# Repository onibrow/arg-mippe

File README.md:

# Modular Integration Platform for Printed Electronics

##  Burn  In

Functional with indicator LEDs to burn in Arduino bootloader to any ISP contact pad enabled microcontroller board.

## MIPPE Base

Two Versions: ATMega328 \& ATMega32U4. The 328 does not have a built in USB interface and has a larger footprint size at a 32 pin QFP. The 32u4 does support native USB with a higher price tag and smaller footprint 44 pin QFN.

To flash, plug in the Burn In tool and run `bootloader.sh` script. Tap on a fully populated microcontrller enabled board using ISP contact pads and pogo pins. Select the appropriate microcontroller to start flashing. The 328 will only take about 15 seconds, while the 32u4 takes an upwards of 2 minutes

## OLED PMIC

An OLED driver that can do current control and limiting.

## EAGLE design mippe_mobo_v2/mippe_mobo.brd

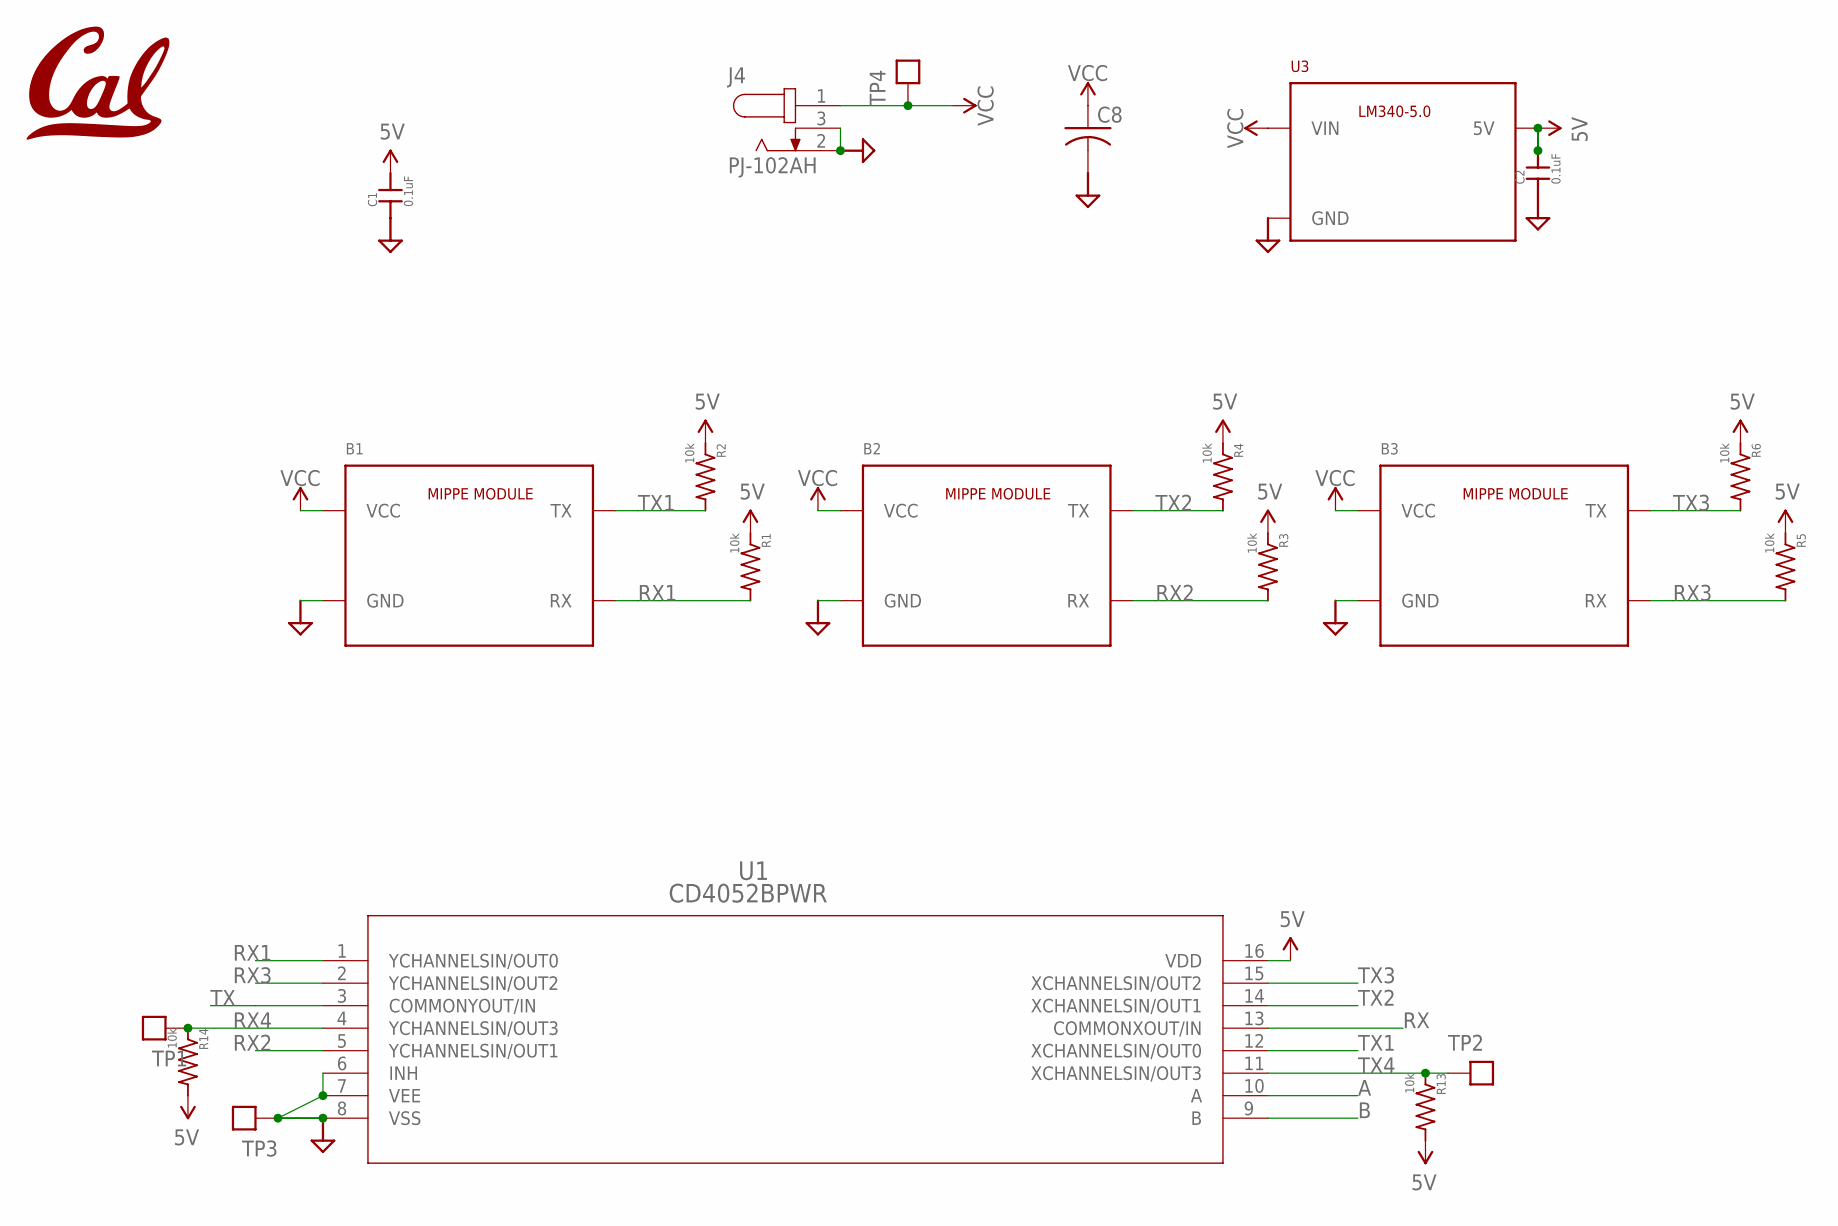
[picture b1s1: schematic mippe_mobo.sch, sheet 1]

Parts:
B1, B2, B3: MIPPE_MOD
C1: 0.1uF; 0402-CAP
C2: 0.1uF; 0603-CAP
C8: CAP_ELEC_3MM_SMD; CAP_3MM
J4: PJ-102AH; CUI_PJ-102AH
L1: UCB_CAL500MIL; UCB_CAL_500MIL
R1, R2, R3, R4, R5, R6, R13, R14: 10k; R0402
TP1, TP2, TP3, TP4: TEST_POINTTHRU; TEST_POINT
U1: CD4052BPWR; PW16
U3: LM340MPX-5.0230; SOT230P700X180-4N

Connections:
5V: C1.2, C2.2, R1.1, R2.1, R3.1, R4.1, R5.1, R6.1, R13.2, R14.2, U1.16 (VDD), U3.3 (5V)
A: U1.10 (A); also elsewhere on the board
B: U1.9 (B); also elsewhere on the board
GND: B1.GND@0 (GND), B1.GND@1 (GND), B1.GND@2 (GND), B1.GND@3 (GND), B2.GND@0 (GND), B2.GND@1 (GND), B2.GND@2 (GND), B2.GND@3 (GND), B3.GND@0 (GND), B3.GND@1 (GND), B3.GND@2 (GND), B3.GND@3 (GND), C1.1, C2.1, C8.NEG, J4.2, J4.3, TP3.1, U1.6 (INH), U1.7 (VEE), U1.8 (VSS), U3.2 (GND), U3.4 (GND); also elsewhere on the board
RX: U1.13 (COMMONXOUT/IN); also elsewhere on the board
RX1: B1.RX, R1.2, U1.1 (YCHANNELSIN/OUT0)
RX2: B2.RX, R3.2, U1.5 (YCHANNELSIN/OUT1)
RX3: B3.RX, R5.2, U1.2 (YCHANNELSIN/OUT2)
RX4: R14.1, TP1.1, U1.4 (YCHANNELSIN/OUT3)
TX: U1.3 (COMMONYOUT/IN); also elsewhere on the board
TX1: B1.TX, R2.2, U1.12 (XCHANNELSIN/OUT0)
TX2: B2.TX, R4.2, U1.14 (XCHANNELSIN/OUT1)
TX3: B3.TX, R6.2, U1.15 (XCHANNELSIN/OUT2)
TX4: R13.1, TP2.1, U1.11 (XCHANNELSIN/OUT3)
VCC: B1.VCC@0 (VCC), B1.VCC@1 (VCC), B1.VCC@2 (VCC), B1.VCC@3 (VCC), B2.VCC@0 (VCC), B2.VCC@1 (VCC), B2.VCC@2 (VCC), B2.VCC@3 (VCC), B3.VCC@0 (VCC), B3.VCC@1 (VCC), B3.VCC@2 (VCC), B3.VCC@3 (VCC), C8.POS, J4.1, TP4.1, U3.1 (VIN)

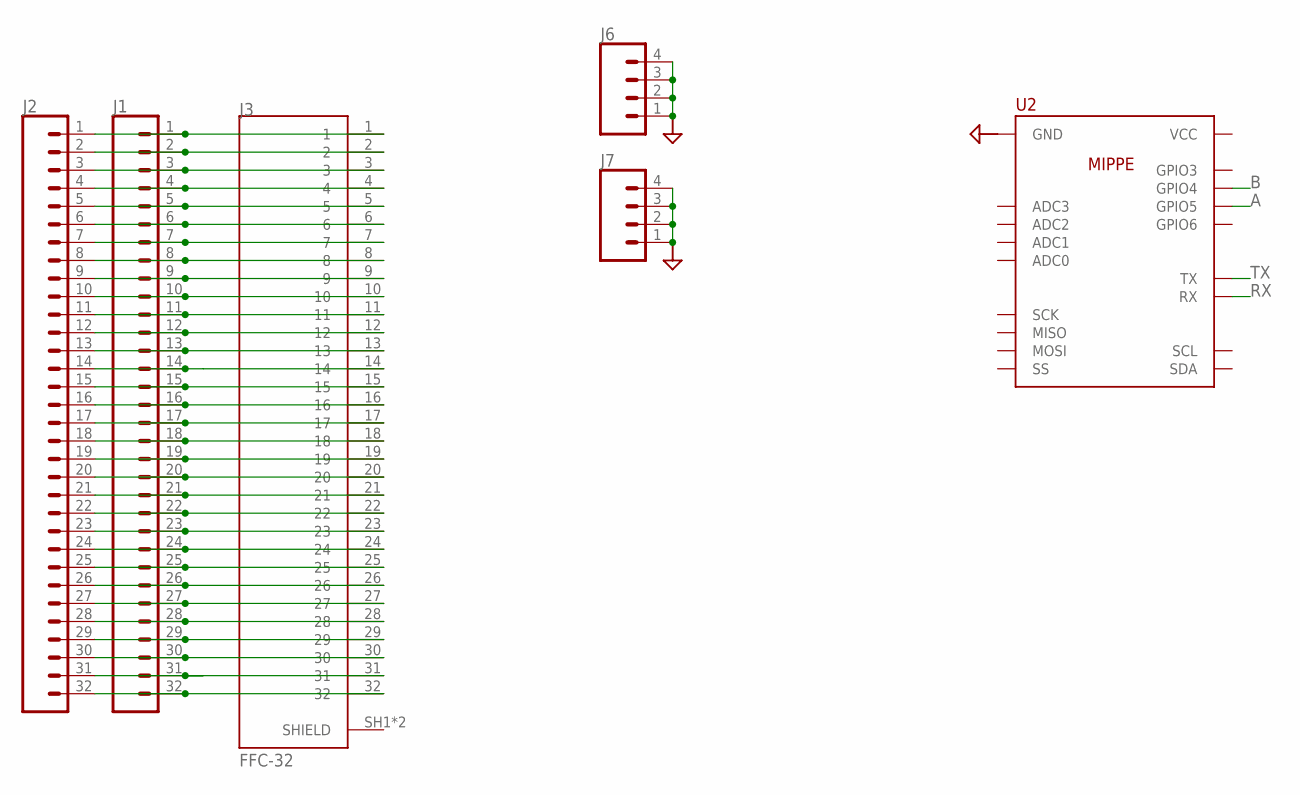
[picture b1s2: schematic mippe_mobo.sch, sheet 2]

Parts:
J1, J2: CONN_32; 1X32
J3: FFC-32; MOLEX_503480-3200
J6, J7: CONN_04; 1X04
U2: MIPPE

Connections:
A: U2.GPIO5; also elsewhere on the board
B: U2.GPIO4; also elsewhere on the board
GND: J6.1, J6.2, J6.3, J6.4, J7.1, J7.2, J7.3, J7.4, U2.GND@0 (GND), U2.GND@1 (GND); also elsewhere on the board
unnamed: J1.1, J2.1, J3.1
unnamed: J1.2, J2.2, J3.2
unnamed: J1.3, J2.3, J3.3
unnamed: J1.4, J2.4, J3.4
unnamed: J1.5, J2.5, J3.5
unnamed: J1.6, J2.6, J3.6
unnamed: J1.7, J2.7, J3.7
unnamed: J1.8, J2.8, J3.8
unnamed: J1.9, J2.9, J3.9
unnamed: J1.10, J2.10, J3.10
unnamed: J1.11, J2.11, J3.11
unnamed: J1.12, J2.12, J3.12
unnamed: J1.13, J2.13, J3.13
unnamed: J1.14, J2.14, J3.14
unnamed: J1.15, J2.15, J3.15
unnamed: J1.16, J2.16, J3.16
unnamed: J1.17, J2.17, J3.17
unnamed: J1.18, J2.18, J3.18
unnamed: J1.19, J2.19, J3.19
unnamed: J1.20, J2.20, J3.20
unnamed: J1.21, J2.21, J3.21
unnamed: J1.22, J2.22, J3.22
unnamed: J1.23, J2.23, J3.23
unnamed: J1.24, J2.24, J3.24
unnamed: J1.25, J2.25, J3.25
unnamed: J1.26, J2.26, J3.26
unnamed: J1.27, J2.27, J3.27
unnamed: J1.28, J2.28, J3.28
unnamed: J1.29, J2.29, J3.29
unnamed: J1.30, J2.30, J3.30
unnamed: J1.31, J2.31, J3.31
unnamed: J1.32, J2.32, J3.32
RX: U2.RX; also elsewhere on the board
TX: U2.TX; also elsewhere on the board

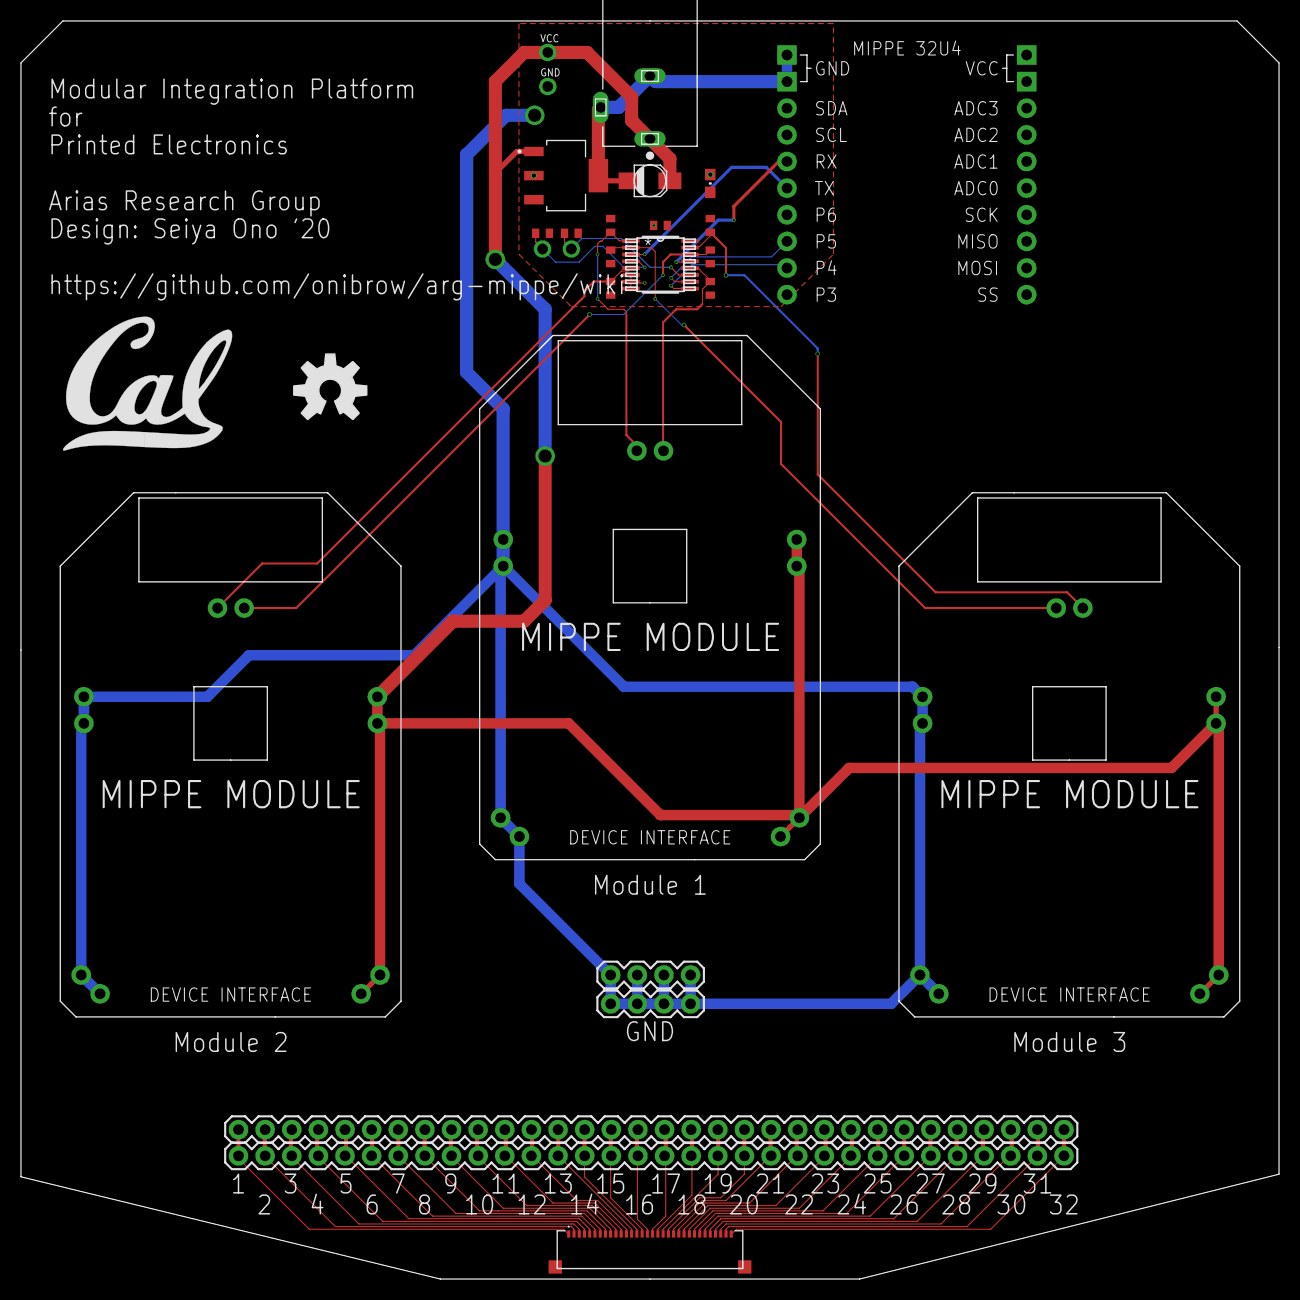
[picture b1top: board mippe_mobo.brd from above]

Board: 2 copper layers, 120.0 x 120.0 mm, 29 parts (0 on the bottom side), 47 nets.

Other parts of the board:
U$17: OSHW-LOGO-L

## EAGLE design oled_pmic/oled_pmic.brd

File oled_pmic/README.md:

# OLED PMIC

Power Management IC OLED Driver Board

Using the [AL5801](https://www.digikey.com/product-detail/en/diodes-incorporated/AL5801W6-7/AL5801W6-7DICT-ND/3481118), we can supply a high voltage (9V) to the OLEDs while controlling the current through it, up to 350mA. To limit the current through Q2 (see figure below) R\_bias must be set to 52.5k when running Vcc = 9V. The sense resistor R\_ext will be set to a minimum of 1.6 Ohms for full 350mA operation.

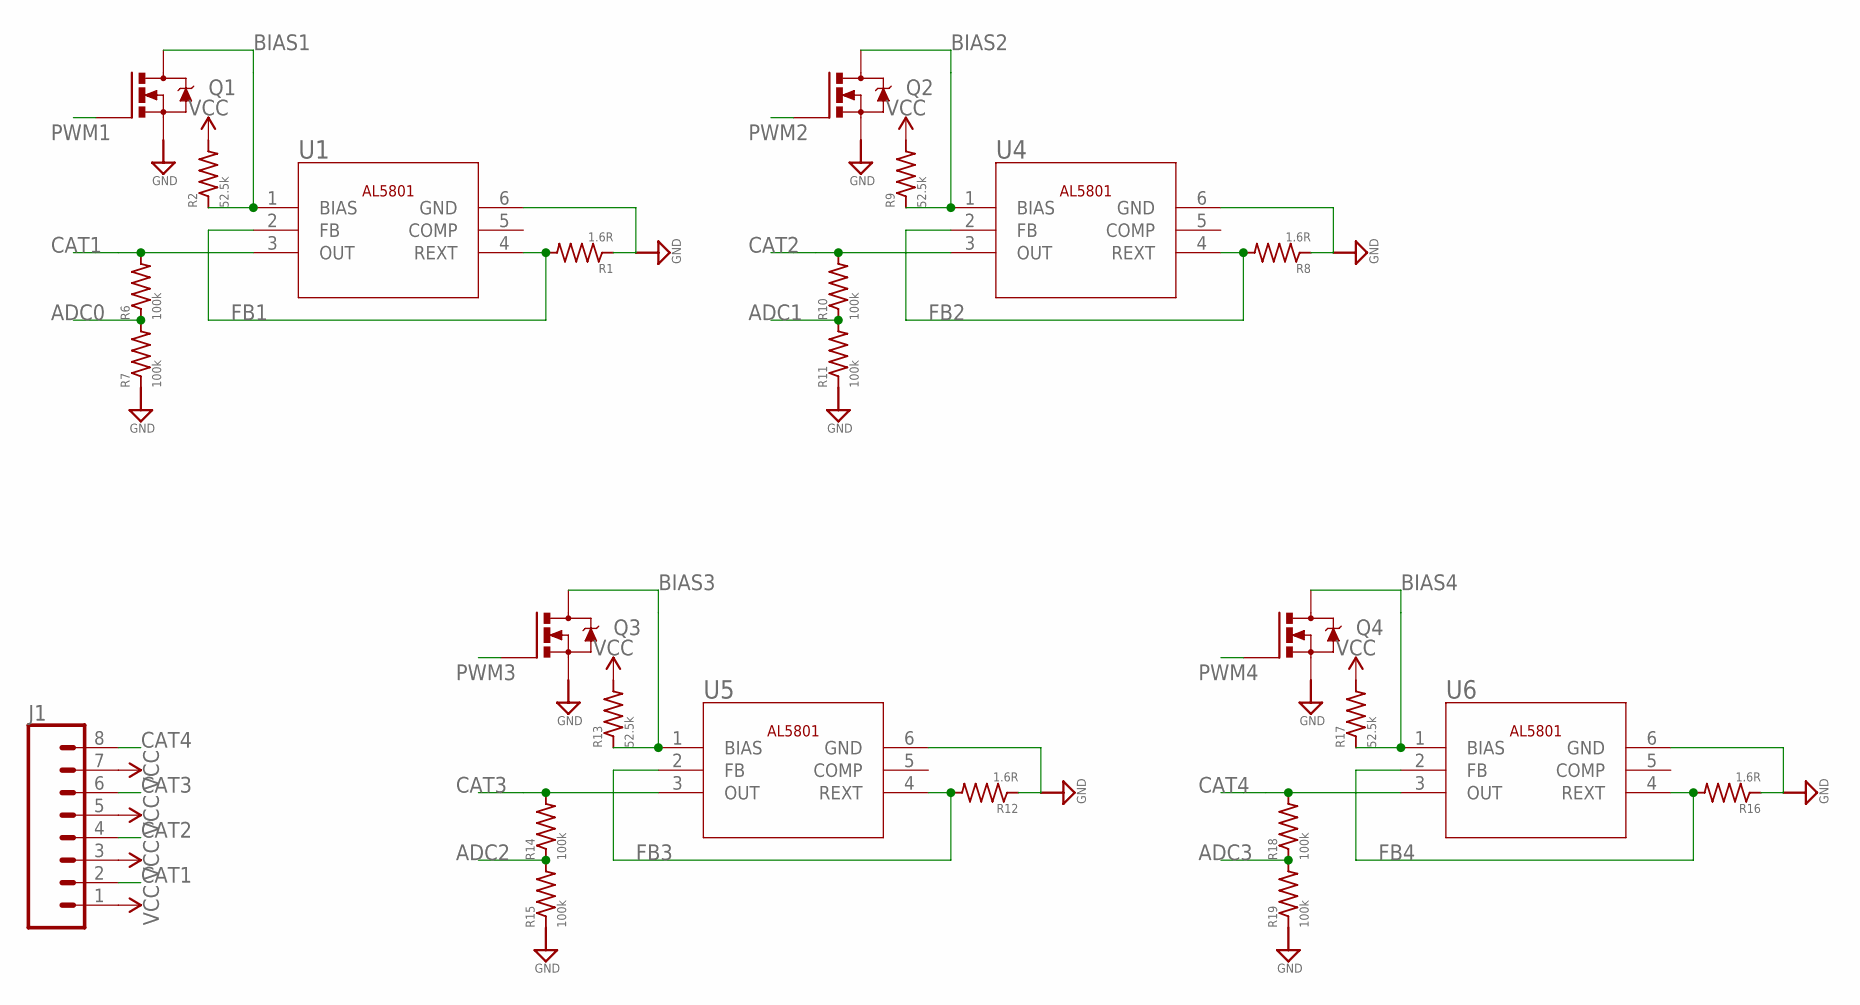
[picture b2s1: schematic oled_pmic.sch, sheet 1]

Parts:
J1: CONN_08"; 1X08
Q1, Q2, Q3, Q4: N-CHANNEL-MOSFETSOT23-3; SOT23-3
R1, R8, R12, R16: 1.6R; 0603-RES
R2, R9, R13, R17: 52.5k; 0603-RES
R6, R7, R10, R11, R14, R15, R18, R19: 100k; R0402
U1, U4, U5, U6: AL5801W6-7; SOT26

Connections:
ADC0: R6.1, R7.2; also elsewhere on the board
ADC1: R10.1, R11.2; also elsewhere on the board
ADC2: R14.1, R15.2; also elsewhere on the board
ADC3: R18.1, R19.2; also elsewhere on the board
BIAS1: Q1.3 (D), R2.1, U1.1 (BIAS)
BIAS2: Q2.3 (D), R9.1, U4.1 (BIAS)
BIAS3: Q3.3 (D), R13.1, U5.1 (BIAS)
BIAS4: Q4.3 (D), R17.1, U6.1 (BIAS)
CAT1: J1.2, R6.2, U1.3 (OUT)
CAT2: J1.4, R10.2, U4.3 (OUT)
CAT3: J1.6, R14.2, U5.3 (OUT)
CAT4: J1.8, R18.2, U6.3 (OUT)
FB1: R1.2, U1.2 (FB), U1.4 (REXT)
FB2: R8.2, U4.2 (FB), U4.4 (REXT)
FB3: R12.2, U5.2 (FB), U5.4 (REXT)
FB4: R16.2, U6.2 (FB), U6.4 (REXT)
GND: Q1.2 (S), Q2.2 (S), Q3.2 (S), Q4.2 (S), R1.1, R7.1, R8.1, R11.1, R12.1, R15.1, R16.1, R19.1, U1.6 (GND), U4.6 (GND), U5.6 (GND), U6.6 (GND); also elsewhere on the board
PWM1: Q1.1 (G); also elsewhere on the board
PWM2: Q2.1 (G); also elsewhere on the board
PWM3: Q3.1 (G); also elsewhere on the board
PWM4: Q4.1 (G); also elsewhere on the board
VCC: J1.1, J1.3, J1.5, J1.7, R2.2, R9.2, R13.2, R17.2; also elsewhere on the board

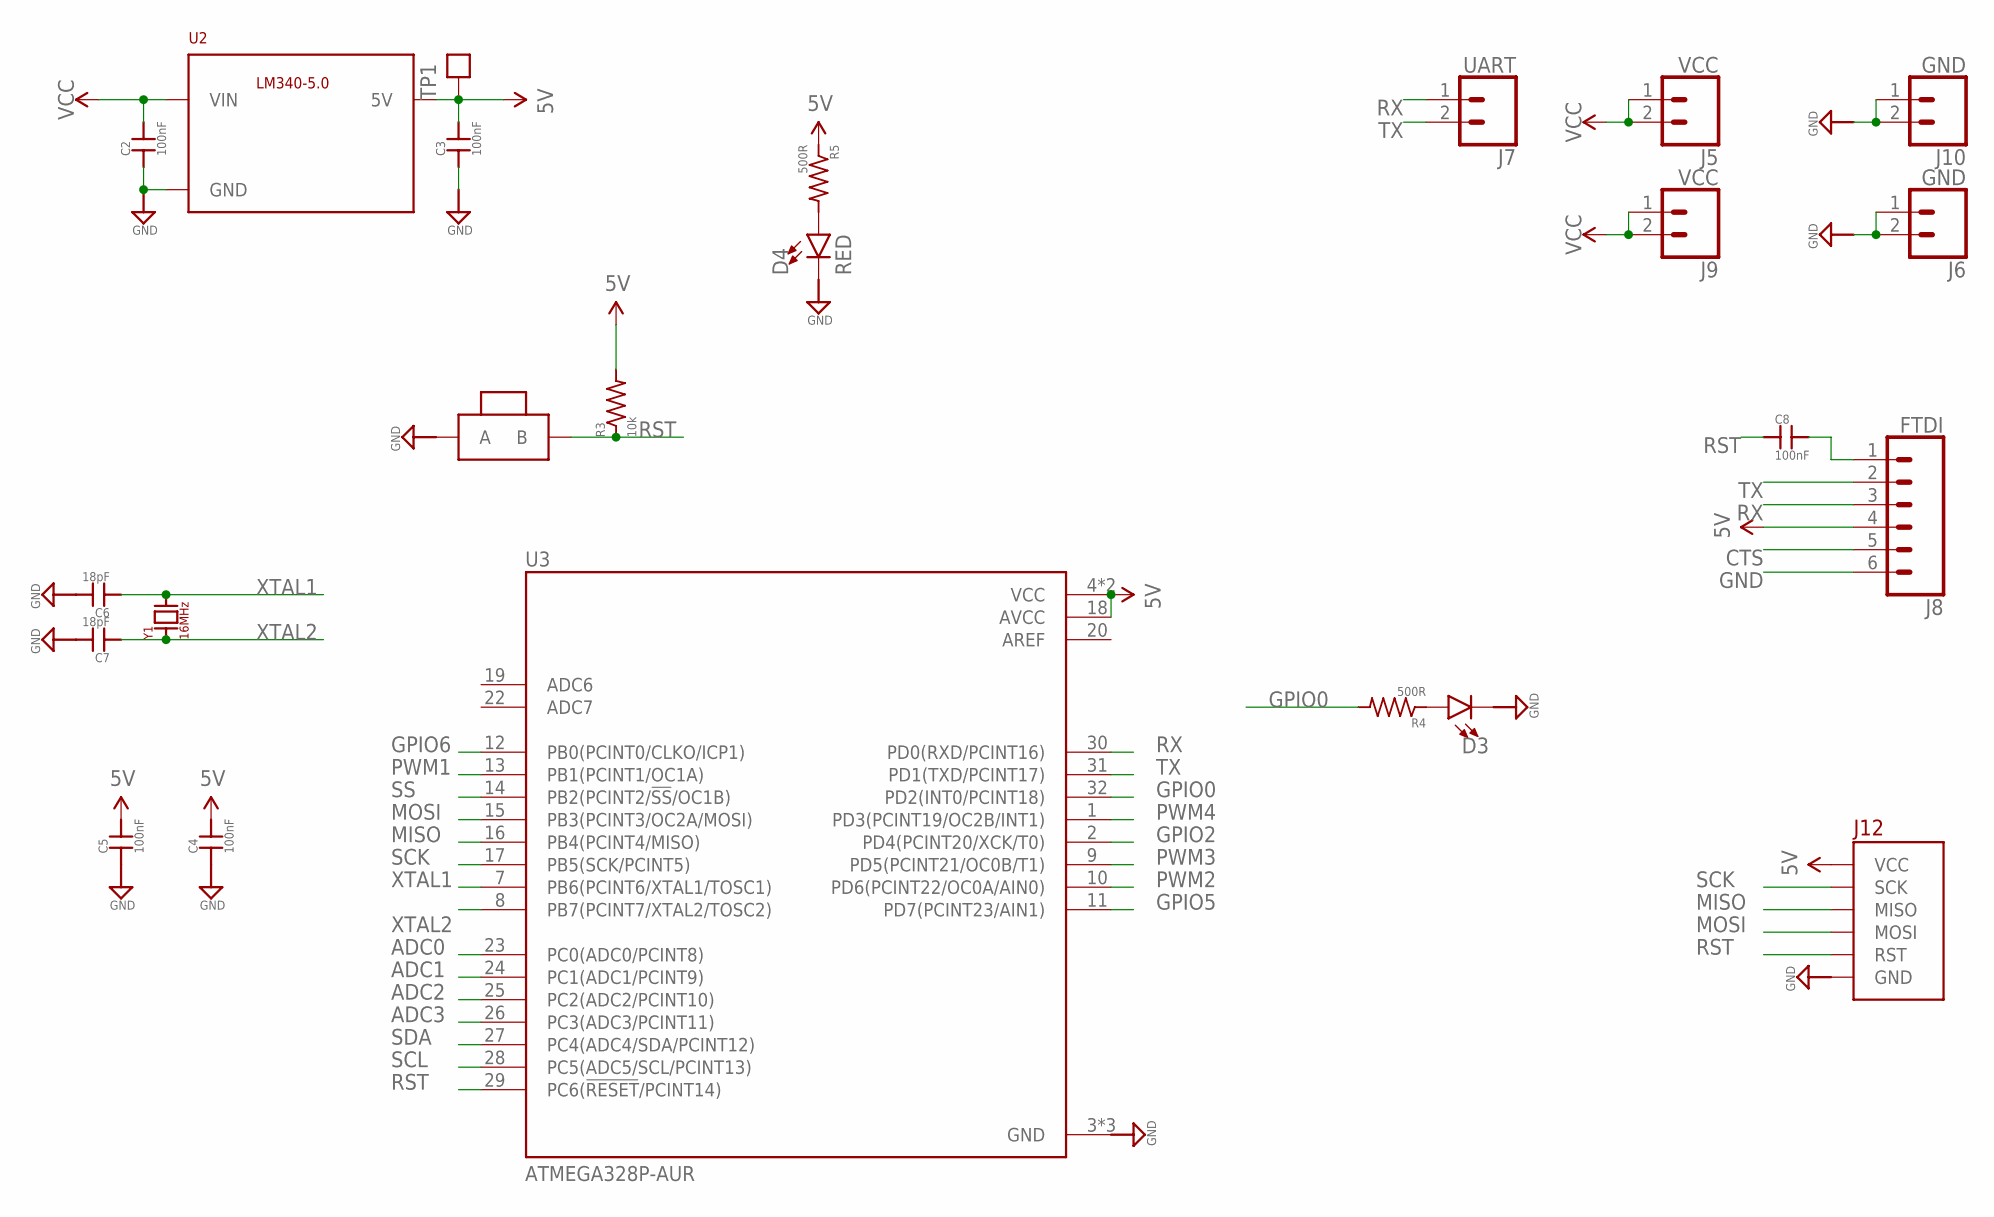
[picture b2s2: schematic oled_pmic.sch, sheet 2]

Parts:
C2, C3, C4, C5, C8: 100nF; 0402-CAP
C6, C7: 18pF; 0402-CAP
D3: LED0603; LED-0603
D4: RED; LED-0603
J5, J9: VCC; 1X02
J6, J10: GND; 1X02
J7: UART; 1X02
J8: FTDI; 1X06_NO_SILK
J12: BURNIN
R3: 10k; R0402
R4, R5: 500R; R0402
SW1: BTN-PTS810; BTN_PTS810
TP1: TEST_POINTTHRU; TEST_POINT
U2: LM340MPX-5.0230; SOT230P700X180-4N
U3: ATMEGA328P-AUR; QFP80P900X900X120-32N
Y1: 16MHz; XTAL500X320X130N

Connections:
5V: C3.2, C4.2, C5.2, J8.4, J12.3.3V (VCC), R3.2, R5.1, TP1.1, U2.3 (5V), U3.4 (VCC), U3.6 (VCC), U3.18 (AVCC)
ADC0: U3.23 (PC0(ADC0/PCINT8)); also elsewhere on the board
ADC1: U3.24 (PC1(ADC1/PCINT9)); also elsewhere on the board
ADC2: U3.25 (PC2(ADC2/PCINT10)); also elsewhere on the board
ADC3: U3.26 (PC3(ADC3/PCINT11)); also elsewhere on the board
AREF: U3.20 (AREF)
CTS: J8.5
GND: C2.1, C3.1, C4.1, C5.1, C6.2, C7.2, D3.C, D4.C, J6.1, J6.2, J8.6, J10.1, J10.2, J12.GND, SW1.1 (A), SW1.2 (A), U2.2 (GND), U2.4 (GND), U3.3 (GND), U3.5 (GND), U3.21 (GND); also elsewhere on the board
GPIO0: R4.2, U3.32 (PD2(INT0/PCINT18))
GPIO2: U3.2 (PD4(PCINT20/XCK/T0))
GPIO5: U3.11 (PD7(PCINT23/AIN1))
GPIO6: U3.12 (PB0(PCINT0/CLKO/ICP1))
MISO: J12.MISO, U3.16 (PB4(PCINT4/MISO))
MOSI: J12.MOSI, U3.15 (PB3(PCINT3/OC2A/MOSI))
unnamed: D3.A, R4.1
unnamed: D4.A, R5.2
unnamed: C8.2, J8.1
PWM1: U3.13 (PB1(PCINT1/OC1A)); also elsewhere on the board
PWM2: U3.10 (PD6(PCINT22/OC0A/AIN0)); also elsewhere on the board
PWM3: U3.9 (PD5(PCINT21/OC0B/T1)); also elsewhere on the board
PWM4: U3.1 (PD3(PCINT19/OC2B/INT1)); also elsewhere on the board
RST: C8.1, J12.RST, R3.1, SW1.3 (B), SW1.4 (B), U3.29 (PC6(!RESET!/PCINT14))
RX: J7.1, J8.3, U3.30 (PD0(RXD/PCINT16))
SCK: J12.SCK, U3.17 (PB5(SCK/PCINT5))
SCL: U3.28 (PC5(ADC5/SCL/PCINT13))
SDA: U3.27 (PC4(ADC4/SDA/PCINT12))
SS: U3.14 (PB2(PCINT2/!SS!/OC1B))
TX: J7.2, J8.2, U3.31 (PD1(TXD/PCINT17))
VCC: C2.2, J5.1, J5.2, J9.1, J9.2, U2.1 (VIN); also elsewhere on the board
XTAL1: C6.1, U3.7 (PB6(PCINT6/XTAL1/TOSC1)), Y1.2 (B)
XTAL2: C7.1, U3.8 (PB7(PCINT7/XTAL2/TOSC2)), Y1.1 (A)

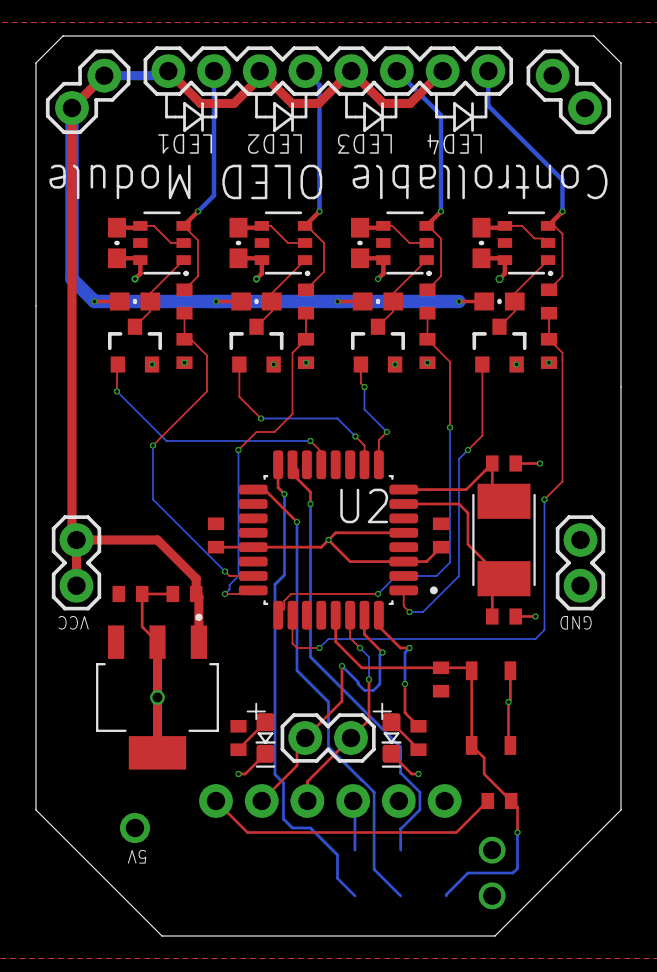
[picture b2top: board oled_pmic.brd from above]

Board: 2 copper layers, 32.5 x 50.0 mm, 49 parts (0 on the bottom side), 35 nets.

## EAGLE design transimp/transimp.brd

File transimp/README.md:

# Transimpedance Amplifier

One of the key applications for a transimpedance amplifier is the readout of a photodiode. The group has looked into using our printed photodiodes in a pulse oximetry setup - meaningful data can only be drawn from [PPG measurements exceeding 60Hz ](https://ieeexplore.ieee.org/stamp/stamp.jsp?arnumber=8704947).

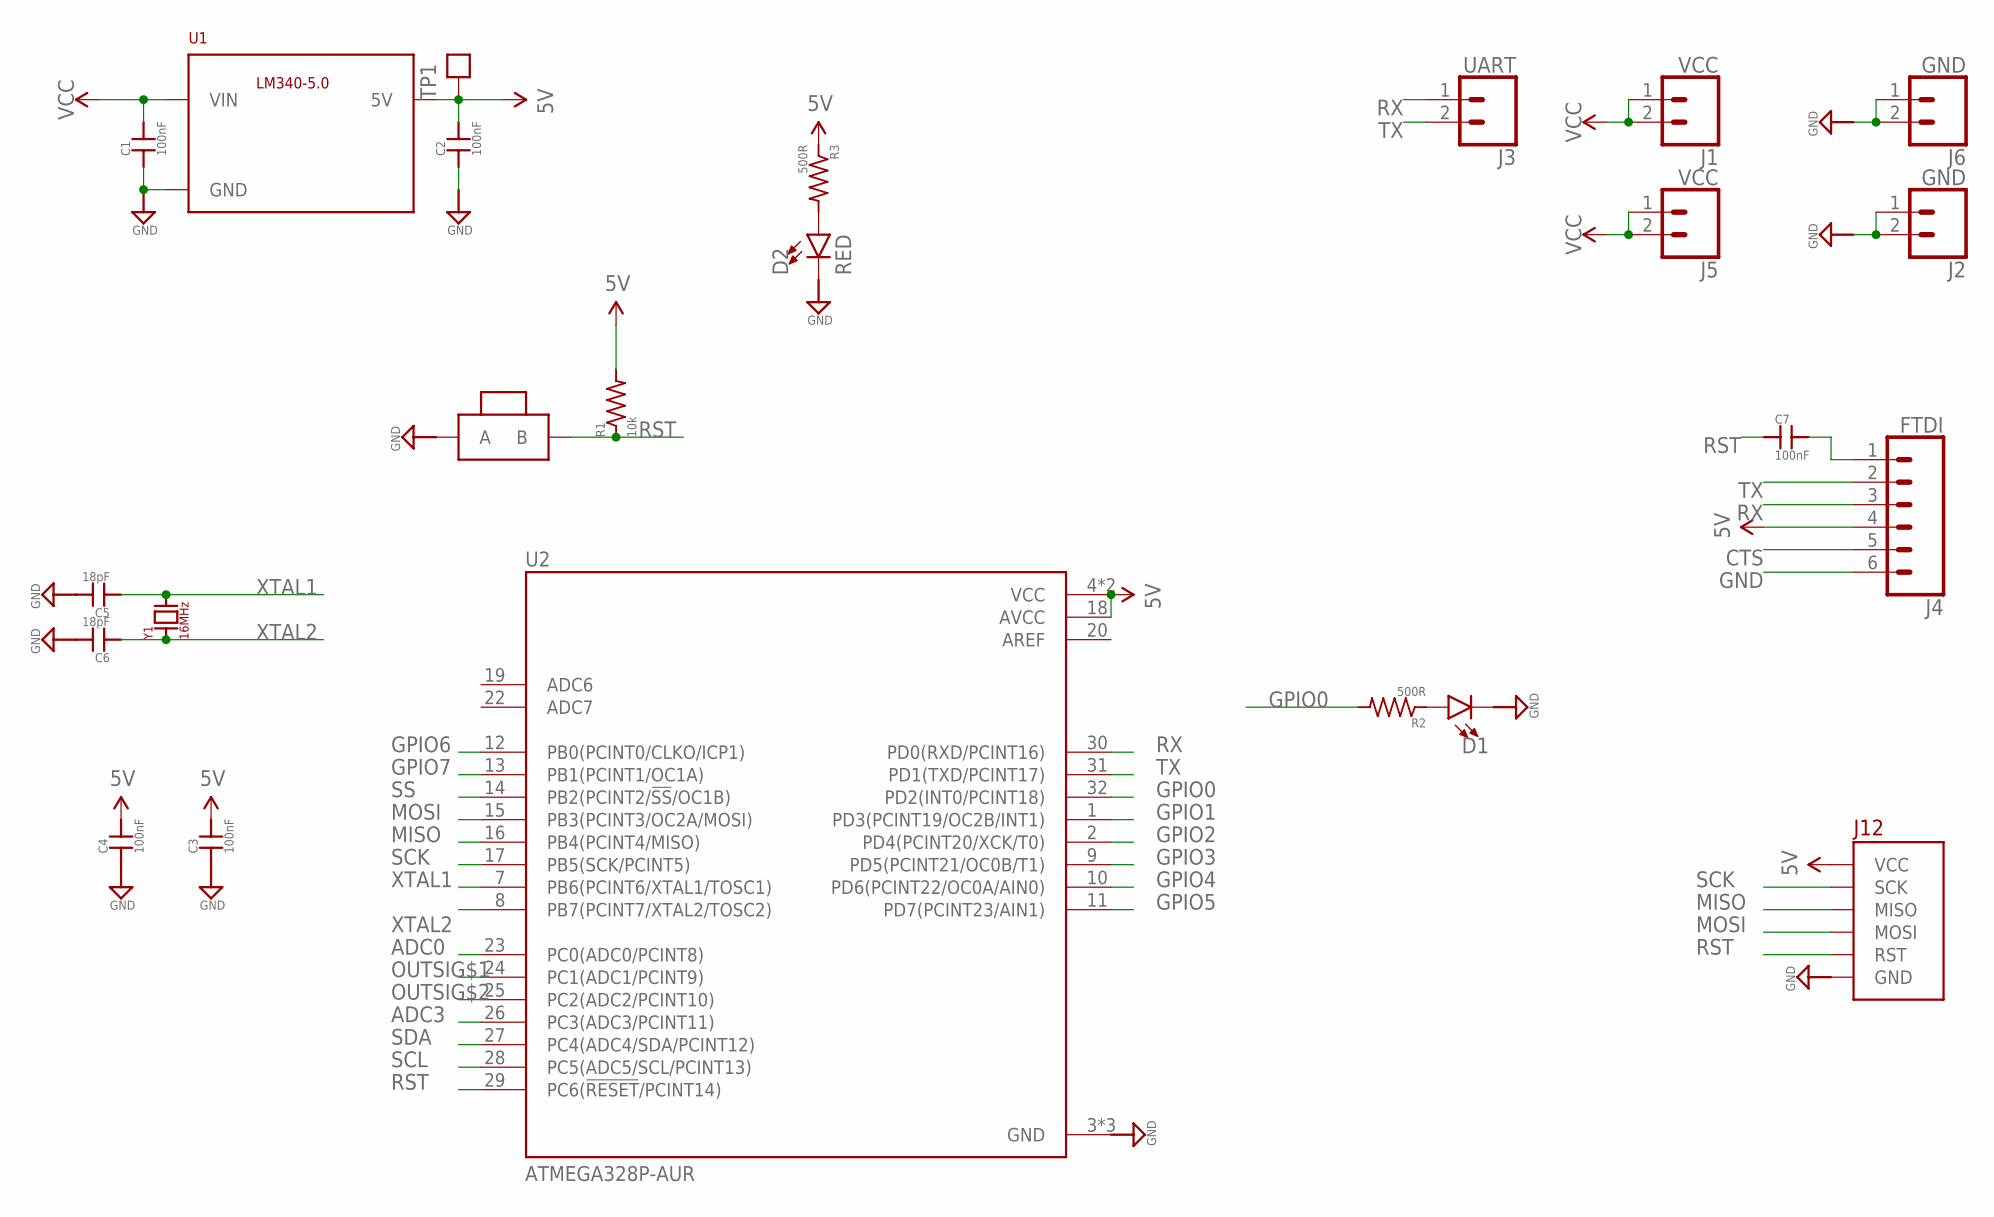
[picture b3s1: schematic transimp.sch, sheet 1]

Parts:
C1, C2, C3, C4, C7: 100nF; 0402-CAP
C5, C6: 18pF; 0402-CAP
D1: LED0603; LED-0603
D2: RED; LED-0603
J1, J5: VCC; 1X02
J2, J6: GND; 1X02
J3: UART; 1X02
J4: FTDI; 1X06_NO_SILK
J12: BURNIN
R1: 10k; R0402
R2, R3: 500R; R0402
SW1: BTN-PTS810; BTN_PTS810
TP1: TEST_POINTTHRU; TEST_POINT
U1: LM340MPX-5.0230; SOT230P700X180-4N
U2: ATMEGA328P-AUR; QFP80P900X900X120-32N
Y1: 16MHz; XTAL500X320X130N

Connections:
5V: C2.2, C3.2, C4.2, J4.4, J12.3.3V (VCC), R1.2, R3.1, TP1.1, U1.3 (5V), U2.4 (VCC), U2.6 (VCC), U2.18 (AVCC); also elsewhere on the board
ADC0: U2.23 (PC0(ADC0/PCINT8))
ADC3: U2.26 (PC3(ADC3/PCINT11))
AREF: U2.20 (AREF)
CTS: J4.5
GND: C1.1, C2.1, C3.1, C4.1, C5.2, C6.2, D1.C, D2.C, J2.1, J2.2, J4.6, J6.1, J6.2, J12.GND, SW1.1 (A), SW1.2 (A), U1.2 (GND), U1.4 (GND), U2.3 (GND), U2.5 (GND), U2.21 (GND); also elsewhere on the board
GPIO0: R2.2, U2.32 (PD2(INT0/PCINT18))
GPIO1: U2.1 (PD3(PCINT19/OC2B/INT1))
GPIO2: U2.2 (PD4(PCINT20/XCK/T0))
GPIO3: U2.9 (PD5(PCINT21/OC0B/T1))
GPIO4: U2.10 (PD6(PCINT22/OC0A/AIN0))
GPIO5: U2.11 (PD7(PCINT23/AIN1))
GPIO6: U2.12 (PB0(PCINT0/CLKO/ICP1))
GPIO7: U2.13 (PB1(PCINT1/OC1A))
MISO: J12.MISO, U2.16 (PB4(PCINT4/MISO))
MOSI: J12.MOSI, U2.15 (PB3(PCINT3/OC2A/MOSI))
unnamed: D1.A, R2.1
unnamed: D2.A, R3.2
unnamed: C7.2, J4.1
OUTSIG$1: U2.24 (PC1(ADC1/PCINT9)); also elsewhere on the board
OUTSIG$2: U2.25 (PC2(ADC2/PCINT10)); also elsewhere on the board
RST: C7.1, J12.RST, R1.1, SW1.3 (B), SW1.4 (B), U2.29 (PC6(!RESET!/PCINT14))
RX: J3.1, J4.3, U2.30 (PD0(RXD/PCINT16))
SCK: J12.SCK, U2.17 (PB5(SCK/PCINT5))
SCL: U2.28 (PC5(ADC5/SCL/PCINT13)); also elsewhere on the board
SDA: U2.27 (PC4(ADC4/SDA/PCINT12)); also elsewhere on the board
SS: U2.14 (PB2(PCINT2/!SS!/OC1B))
TX: J3.2, J4.2, U2.31 (PD1(TXD/PCINT17))
VCC: C1.2, J1.1, J1.2, J5.1, J5.2, U1.1 (VIN)
XTAL1: C5.1, U2.7 (PB6(PCINT6/XTAL1/TOSC1)), Y1.2 (B)
XTAL2: C6.1, U2.8 (PB7(PCINT7/XTAL2/TOSC2)), Y1.1 (A)

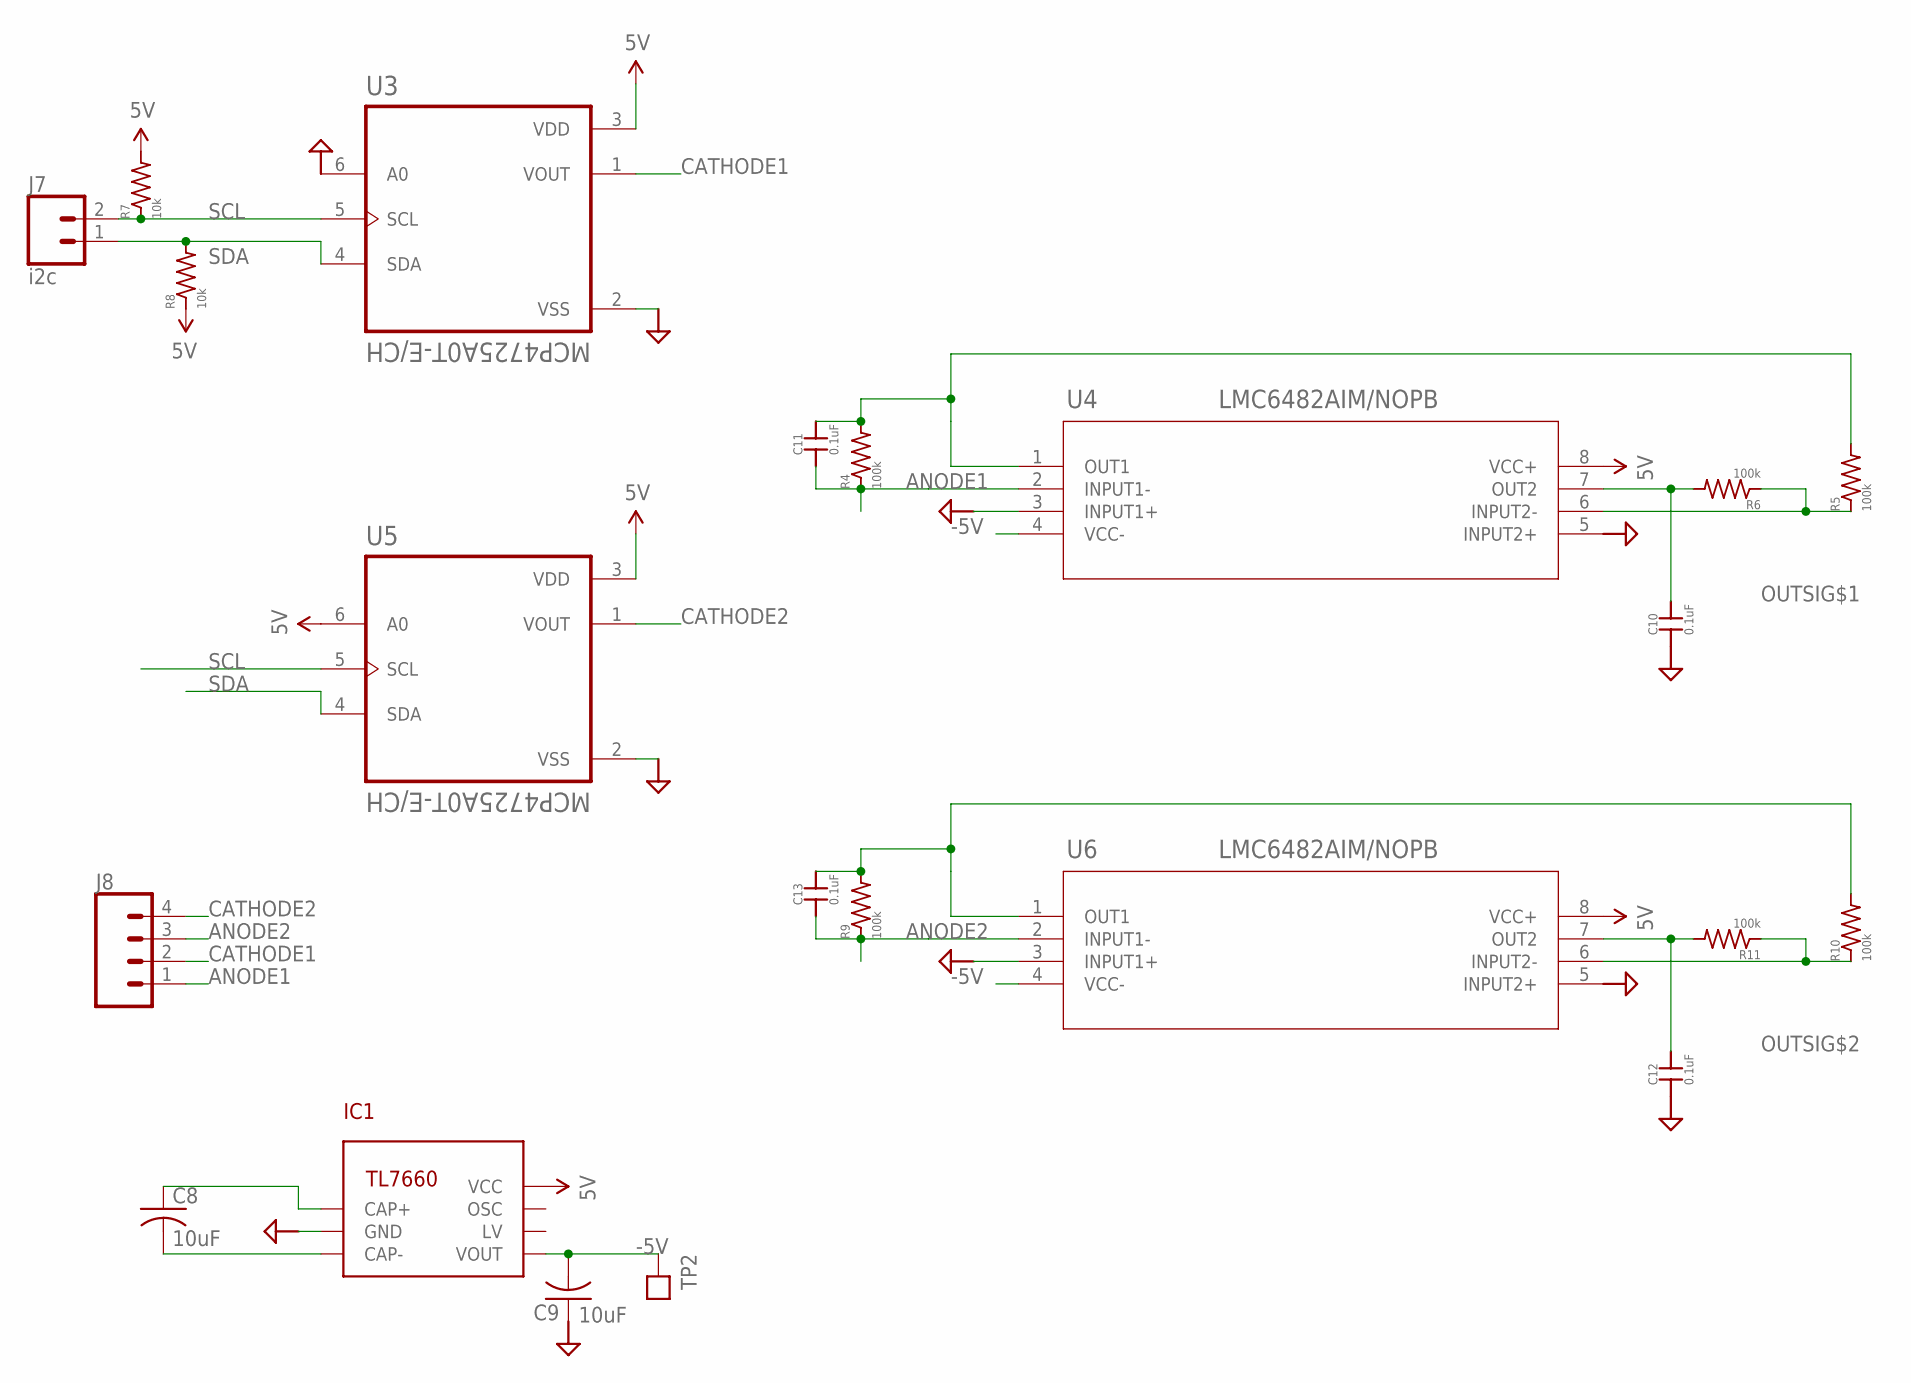
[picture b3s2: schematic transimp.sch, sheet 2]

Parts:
C8, C9: 10uF; CAP_3MM
C10, C11, C12, C13: 0.1uF; 0402-CAP
IC1: TL7660; 8SOICW
J7: i2c; 1X02
J8: CONN_04; 1X04
R4, R5, R6, R9, R10, R11: 100k; R0402
R7, R8: 10k; R0402
TP2: TEST_POINTTHRU; TEST_POINT
U3, U5: MCP4725A0T-E/CH; SOT95P270X145-6N
U4, U6: LMC6482AIM/NOPB; M08A

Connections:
5V: IC1.8 (VCC), R7.2, R8.1, U3.3 (VDD), U4.8 (VCC+), U5.3 (VDD), U5.6 (A0), U6.8 (VCC+); also elsewhere on the board
-5V: C9.NEG, IC1.5 (VOUT), TP2.1, U4.4 (VCC-), U6.4 (VCC-)
ANODE1: C11.1, J8.1, R4.1, U4.2 (INPUT1-)
ANODE2: C13.1, J8.3, R9.1, U6.2 (INPUT1-)
CATHODE1: J8.2, U3.1 (VOUT)
CATHODE2: J8.4, U5.1 (VOUT)
GND: C9.POS, C10.1, C12.1, IC1.3 (GND), U3.2 (VSS), U3.6 (A0), U4.3 (INPUT1+), U4.5 (INPUT2+), U5.2 (VSS), U6.3 (INPUT1+), U6.5 (INPUT2+); also elsewhere on the board
unnamed: C8.POS, IC1.2 (CAP+)
unnamed: C8.NEG, IC1.4 (CAP-)
unnamed: C13.2, R9.2, R10.2, U6.1 (OUT1)
unnamed: C11.2, R4.2, R5.2, U4.1 (OUT1)
unnamed: R5.1, R6.1, U4.6 (INPUT2-)
unnamed: R10.1, R11.1, U6.6 (INPUT2-)
OUTSIG$1: C10.2, R6.2, U4.7 (OUT2); also elsewhere on the board
OUTSIG$2: C12.2, R11.2, U6.7 (OUT2); also elsewhere on the board
SCL: J7.2, R7.1, U3.5 (SCL), U5.5 (SCL); also elsewhere on the board
SDA: J7.1, R8.2, U3.4 (SDA), U5.4 (SDA); also elsewhere on the board

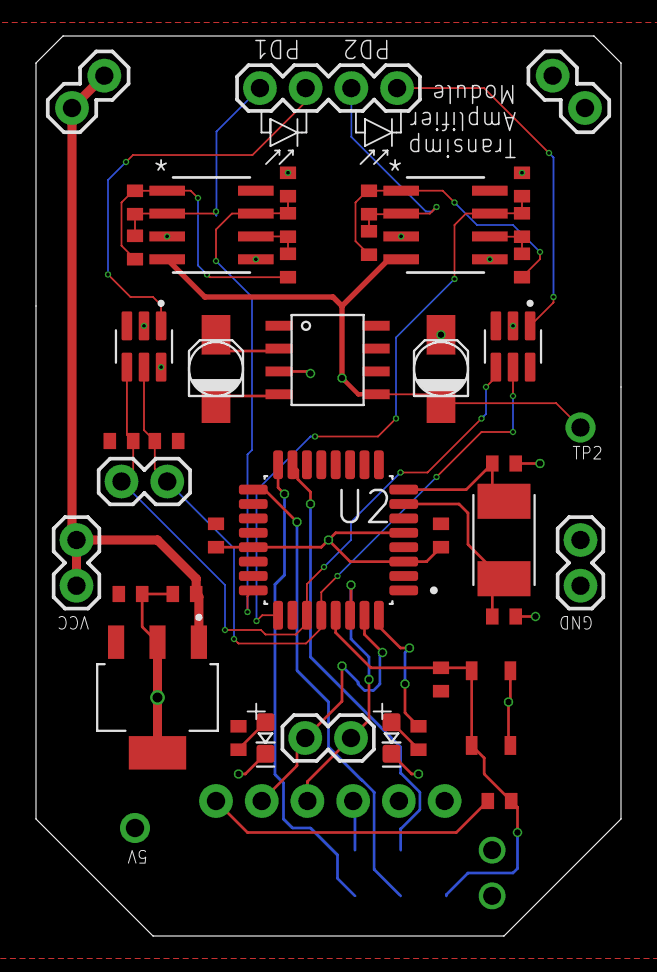
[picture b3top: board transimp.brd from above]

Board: 2 copper layers, 32.5 x 50.0 mm, 46 parts (0 on the bottom side), 30 nets.

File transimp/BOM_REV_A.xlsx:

Comment | Designator | Footprint | LCSC Part #（optional）
ATMEGA328P | U2 | TQFP-32_7.0x7.0x0.8P | C14877
0.1uF | C1, C2, C3, C4, C7, C10, C11,C12, C13 | 0402 | C1525
18pF | C5, C6 | 0402 | C1549
10k | R1, R7, R8 | 0402 | C25744
100k | R4, R5, R6, R9, R10, R11 | 0402 | C25741
500R | R2, R3 | 0402 | C25082
RED LED | D1, D2 | LED_0603 | C2286
